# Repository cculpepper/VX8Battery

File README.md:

This is a printed and PCB'ed battery for the VX8DR. 

I've been using it for approx 2 days now, and it seems to work great. 

I printed the case, backPlate/VX8PrintedCase-WithLightPipes.stl in PLA, 0.15mm. The 0.15 or smaller seems to be important for the clips, so you have more walls. It features two heat-serts for M3 screws for the beltclip. You may want to trim with a file the clips and the passive end clips, but I did not need to. The light pipes were made of 1.75mm clear PETG, and I had to drill them out to 2mm in post. The USB-C hole fits all of my cables, and is probably a bit too big so you'll have to fish around in there to plug it in. 

I had the PCB made up in 0.8mm from JLCPCB, seems to work great, but does bend a bit. The SMT nuts are from adafruit, https://www.adafruit.com/product/4207 . These work great. The interactive bom is in the circuit folder, and should have relevant manufacturer PNs from Digikey, except for the jellybean parts. The chip will charge at 1.2A from the 5V line, and will /eventually/ balance unbalanced cells. There is NO PROTECTION between the cells and the radio interface, so you should use protected cells...

After soldering, you'll need to grind or file the battery clips, SMT nuts, and thermistor to not protrude. IT IS IMPORTANT TO INSULATE THE BACK OF THE PCB. I used 2 layers of kapton. Don't screw this up! 
Also you'll need to trim the "bottom" of the attached PCB, you'll see that it doesn't fit into the 3d printed case. When I up the PCB version, I'll fix that. 

For assembly, I found the easiest thing (after testing the cells fit) is to put the cells into the case in the right orientation, then put the PCB with the battery clips in, "catching" the batteries. Then you can put in the M3 screws into the SMT nuts.

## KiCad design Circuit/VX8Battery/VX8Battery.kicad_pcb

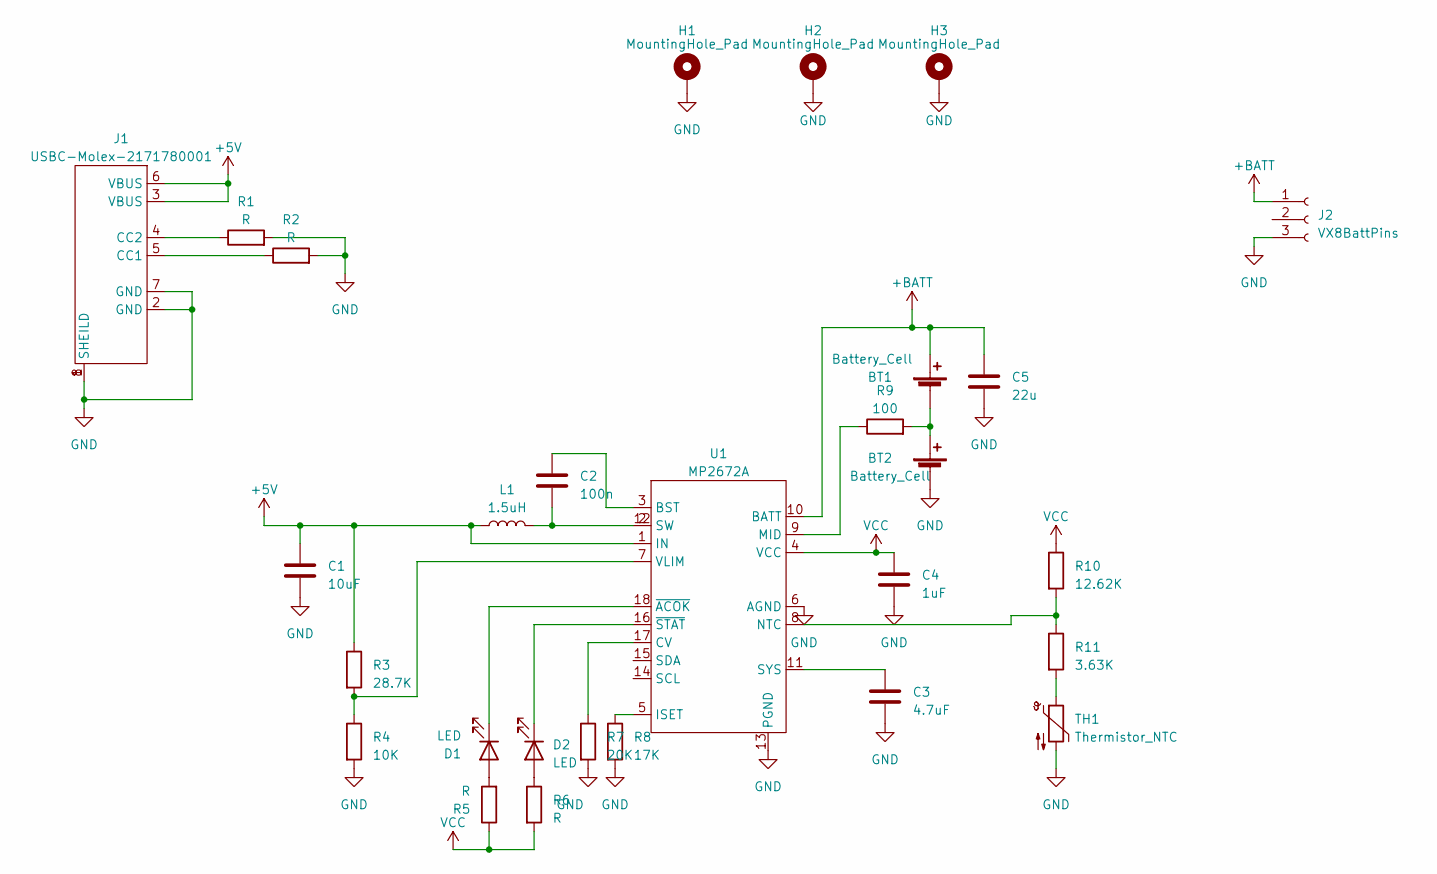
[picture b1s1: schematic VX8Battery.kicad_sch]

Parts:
BT1, BT2: Battery_Cell; 21700Battery
C1: 10uF; C_1210_3225Metric
C2: 100n; C_0603_1608Metric
C3: 4.7uF; C_1206_3216Metric
C4: 1uF; C_0805_2012Metric
C5: 22u; C_1210_3225Metric; Manufacturer PN GRM21BR61E226ME44K
D1, D2: LED; LED_0603_1608Metric
H1, H2, H3: MountingHole_Pad; AdafruitSMTStandoff
J1: USBC-Molex-2171780001; Molex-2171780001
J2: VX8BattPins; VX8BatteryPins
L1: 1.5uH; L_Taiyo-Yuden_NR-50xx_HandSoldering; Manufacturer PN TYS50402R2N-10
R1, R2, R5, R6: R; R_0603_1608Metric
R3: 28.7K; R_0603_1608Metric
R4: 10K; R_0603_1608Metric
R7: 20K; R_0603_1608Metric
R8: 17K; R_0603_1608Metric
R9: 100; R_0603_1608Metric
R10: 12.62K; R_0603_1608Metric
R11: 3.63K; R_0603_1608Metric
TH1: Thermistor_NTC; R_Axial_DIN0204_L3.6mm_D1.6mm_P2.54mm_Vertical; Manufacturer PN NTCLE101E3C90173
U1: MP2672A

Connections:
+5V: C1.1, J1.3 (VBUS), J1.6 (VBUS), L1.1, R3.1, U1.1 (IN)
+BATT: BT1.1 (+), C5.1, J2.1, U1.10 (BATT)
GND: BT2.2 (-), C1.2, C3.2, C4.2, C5.2, H1.1, H2.1, H3.1, J1.1 (SHEILD), J1.2 (GND), J1.7 (GND), J1.8 (SHEILD), J2.3, R1.2, R2.2, R4.2, R7.2, R8.2, TH1.2, U1.6 (AGND), U1.13 (PGND)
unnamed: BT1.2 (-), BT2.1 (+), R9.2
unnamed: C2.1, L1.2, U1.2 (SW), U1.12 (SW)
unnamed: C2.2, U1.3 (BST)
unnamed: C3.1, U1.11 (SYS)
unnamed: D1.2 (A), R5.2
unnamed: D2.2 (A), R6.1
unnamed: J1.4 (CC2), R1.1
unnamed: J1.5 (CC1), R2.1
unnamed: R3.2, R4.1, U1.7 (VLIM)
unnamed: R7.1, U1.17 (CV)
unnamed: R8.1, U1.5 (ISET)
unnamed: R9.1, U1.9 (MID)
unnamed: R10.2, R11.1, U1.8 (NTC)
unnamed: R11.2, TH1.1
unnamed: D2.1 (K), U1.16 (~STAT)
unnamed: D1.1 (K), U1.18 (~ACOK)
VCC: C4.1, R5.1, R6.2, R10.1, U1.4 (VCC)

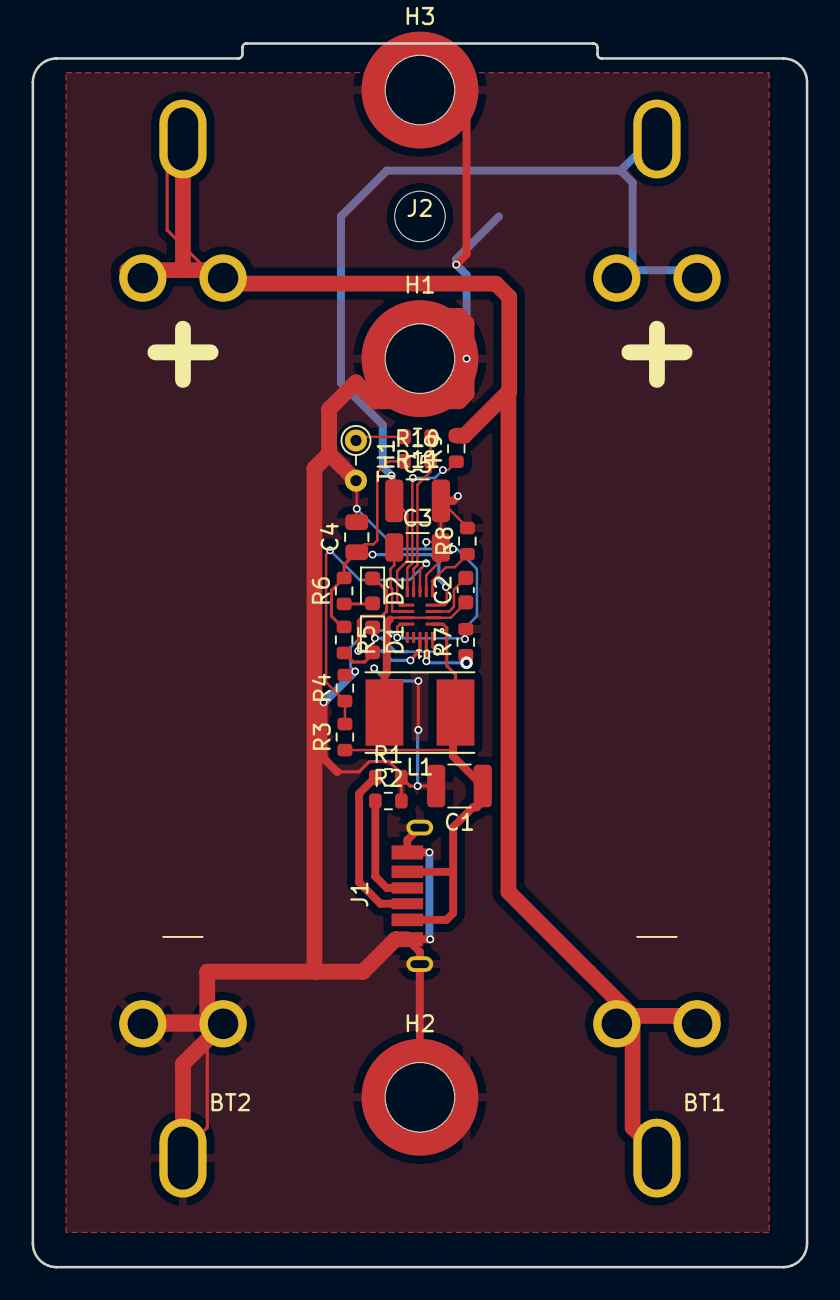
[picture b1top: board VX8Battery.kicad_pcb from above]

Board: 2 copper layers, 49.0 x 77.4 mm, 28 parts (0 on the bottom side), 20 nets.

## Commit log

2021-05-31 Fixed up the battery case, and I wanted to commit before I eff it up again
2021-06-01 Should be the right clearances, but am making one change which might f things up again...
2021-06-01 I think I fixed the printed case... I think something was corrupted. Hopefully I have no changes to make....
2021-06-01 Modified the VX8 clips. Seems to be very delicate, bet edits can be made
2021-06-01 More printed case updates, changing something earlier in the tree keeps screwing up later things, but that seems not bad to fix.
2021-06-01 More clip adjustments
2021-06-02 More optimizations, commiting before trying to move clip to bottom.
2021-06-05 Mostly circuit board updates. Still need to fix the dependency chart for the case
2021-06-17 Should be the finished version, at least finished enough for prod
2021-06-17 Added stl, removed backups
2021-06-19 Added BOM
2021-06-20 Added a belt clip
2021-06-20 Added a readme
2021-06-20 Added note about trimming PCB
